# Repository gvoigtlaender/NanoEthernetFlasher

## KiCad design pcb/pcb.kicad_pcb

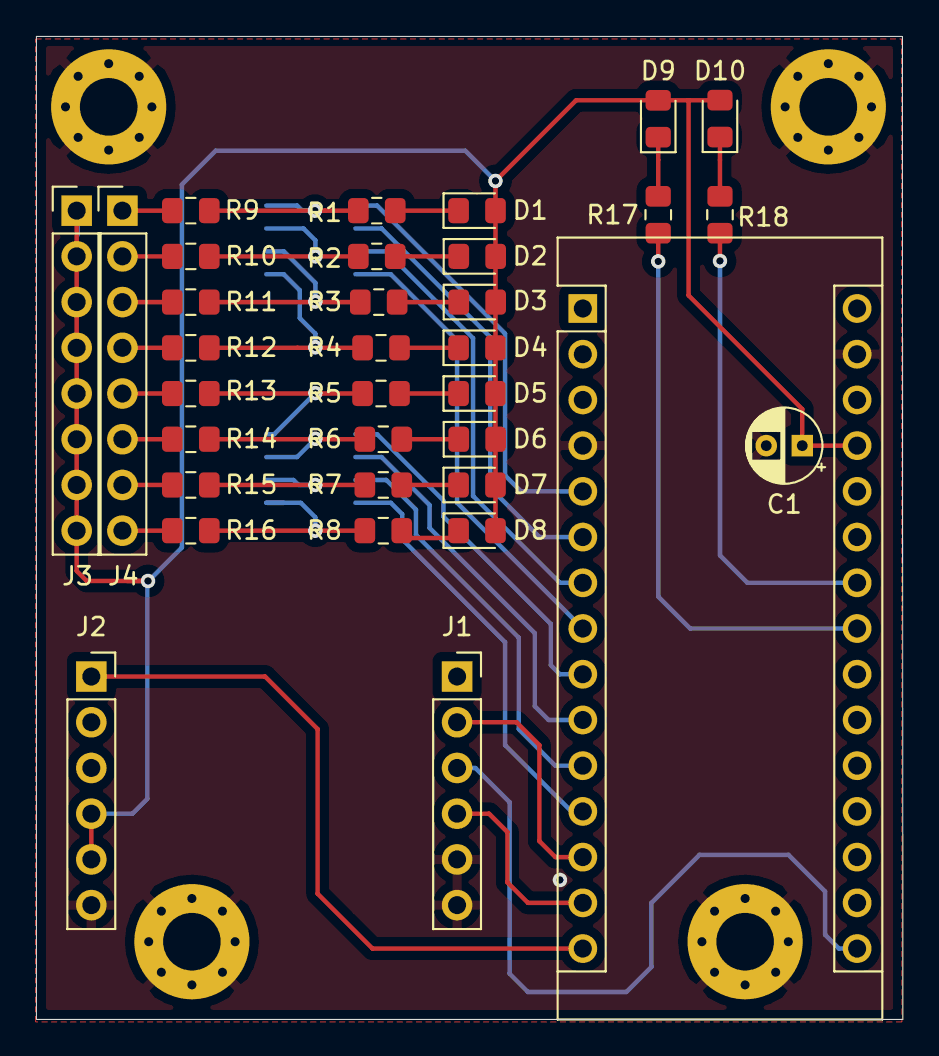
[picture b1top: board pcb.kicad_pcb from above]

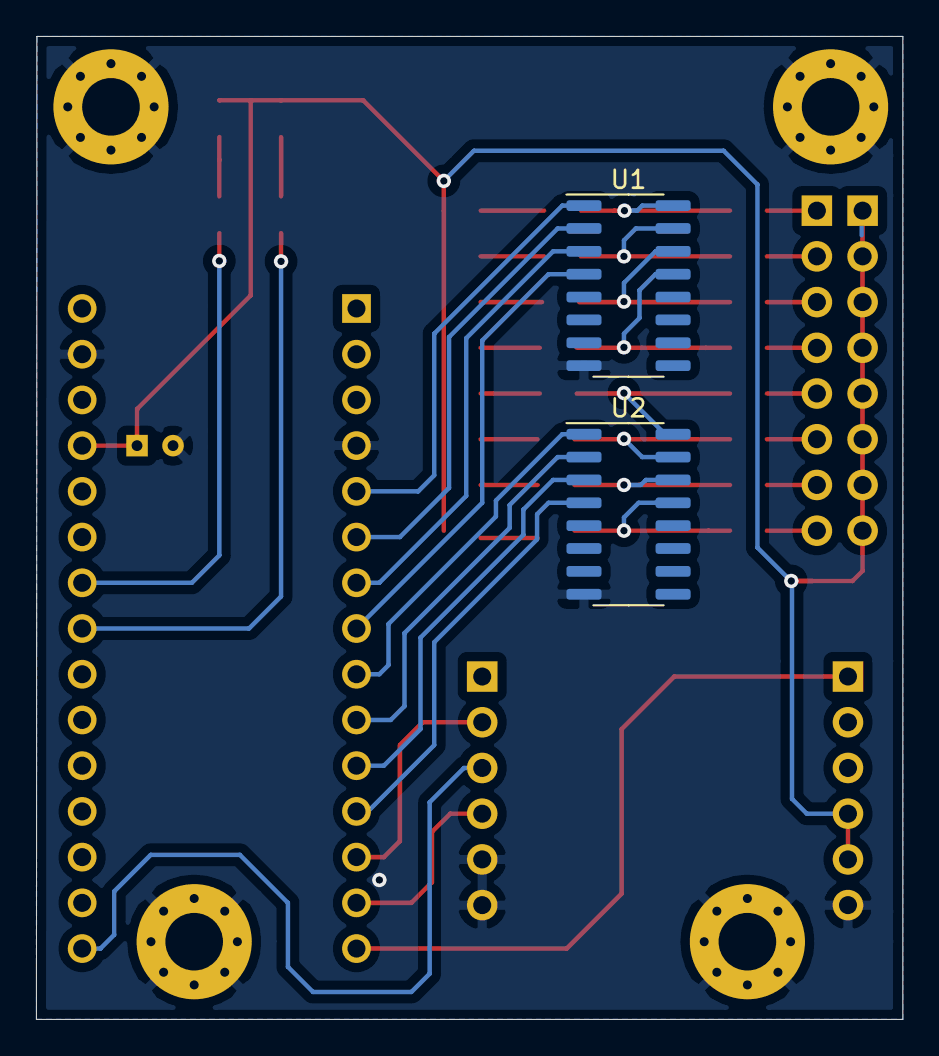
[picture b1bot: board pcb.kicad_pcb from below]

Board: 2 copper layers, 48.1 x 54.6 mm, 40 parts (2 on the bottom side), 42 nets.

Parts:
A1: Arduino_Nano_v3.x; Arduino_Nano
C1: CP; CP_Radial_D4.0mm_P2.00mm
D1, D2, D3, D4, D5, D6, D7, D8, D9, D10: LED; LED_0805_2012Metric_Pad1.15x1.40mm_HandSolder
H1, H2, H3, H4: MountingHole_Pad; MountingHole_3.2mm_M3_Pad_Via
J1, J2: Conn_01x06; PinSocket_1x06_P2.54mm_Vertical
J3, J4: Conn_01x08; PinHeader_1x08_P2.54mm_Vertical
R1, R2, R3, R4, R5, R6, R7, R8, R9, R10, R11, R12, R13, R14, R15, R16, R17, R18: 10k; R_0805_2012Metric_Pad1.15x1.40mm_HandSolder
U1, U2: ULN2003A; SOIC-16_3.9x9.9mm_P1.27mm

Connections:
/5V0: A1.27, C1.1, D1.2, D2.2, D3.2, D4.2, D5.2, D6.2, D7.2, D8.2, D9.2, D10.2, J2.4, J2.5, J3.1, J3.2, J3.3, J3.4, J3.5, J3.6, J3.7, J3.8
/CS: A1.13, J1.2
/D2: A1.5, U1.1
/D3: A1.6, U1.2
/D4: A1.7, U1.3
/D5: A1.8, U1.4
/D6: A1.9, U2.1
/D7: A1.10, U2.2
/D8: A1.11, U2.3
/D9: A1.12, U2.4
/MI: A1.15, J2.1
/MO: A1.14, J1.4
/O1: R1.2, R9.1, U1.16
/O2: R2.2, R10.1, U1.15
/O3: R3.2, R11.1, U1.14
/O4: R4.2, R12.1, U1.13
/O5: R5.2, R13.1, U2.16
/O6: R6.2, R14.1, U2.15
/O7: R7.2, R15.1, U2.14
/O8: R8.2, R16.1, U2.13
/SCK: A1.16, J1.3
/TCP_RCV: A1.23, R17.2
/TCP_SND: A1.24, R18.2
GND: A1.4, A1.29, C1.2, H1.1, H2.1, H3.1, H4.1, J1.5, J1.6, J2.6, U1.8, U2.8
unnamed: D1.1, R1.1
unnamed: D2.1, R2.1
unnamed: D3.1, R3.1
unnamed: D4.1, R4.1
unnamed: D5.1, R5.1
unnamed: D6.1, R6.1
unnamed: D7.1, R7.1
unnamed: D8.1, R8.1
unnamed: D9.1, R17.1
unnamed: D10.1, R18.1
unnamed: J4.1, R9.2
unnamed: J4.2, R10.2
unnamed: J4.3, R11.2
unnamed: J4.4, R12.2
unnamed: J4.5, R13.2
unnamed: J4.6, R14.2
unnamed: J4.7, R15.2
unnamed: J4.8, R16.2
